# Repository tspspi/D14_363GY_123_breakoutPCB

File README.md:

# Breakout board for D14-363GY/123 CRT

This is a simple breakout board that includes impedance
matching networks (in this case tunes for 202 MHz - note
that this lies outside the specs for this tube) for deflection
plates and routes the high voltage and filament currents
to a DB9 connector. This PCB will be used as a mounting
structure for the CRT in a specific application (that
has nothing to do with running an oscilloscope or
visualizing signals)

The (inofficial) symbol and footprint used for the
D14-363GY/123 CRT pin layout is available in an
extra [KiCAD library](https://github.com/tspspi/tspikicadlibs)

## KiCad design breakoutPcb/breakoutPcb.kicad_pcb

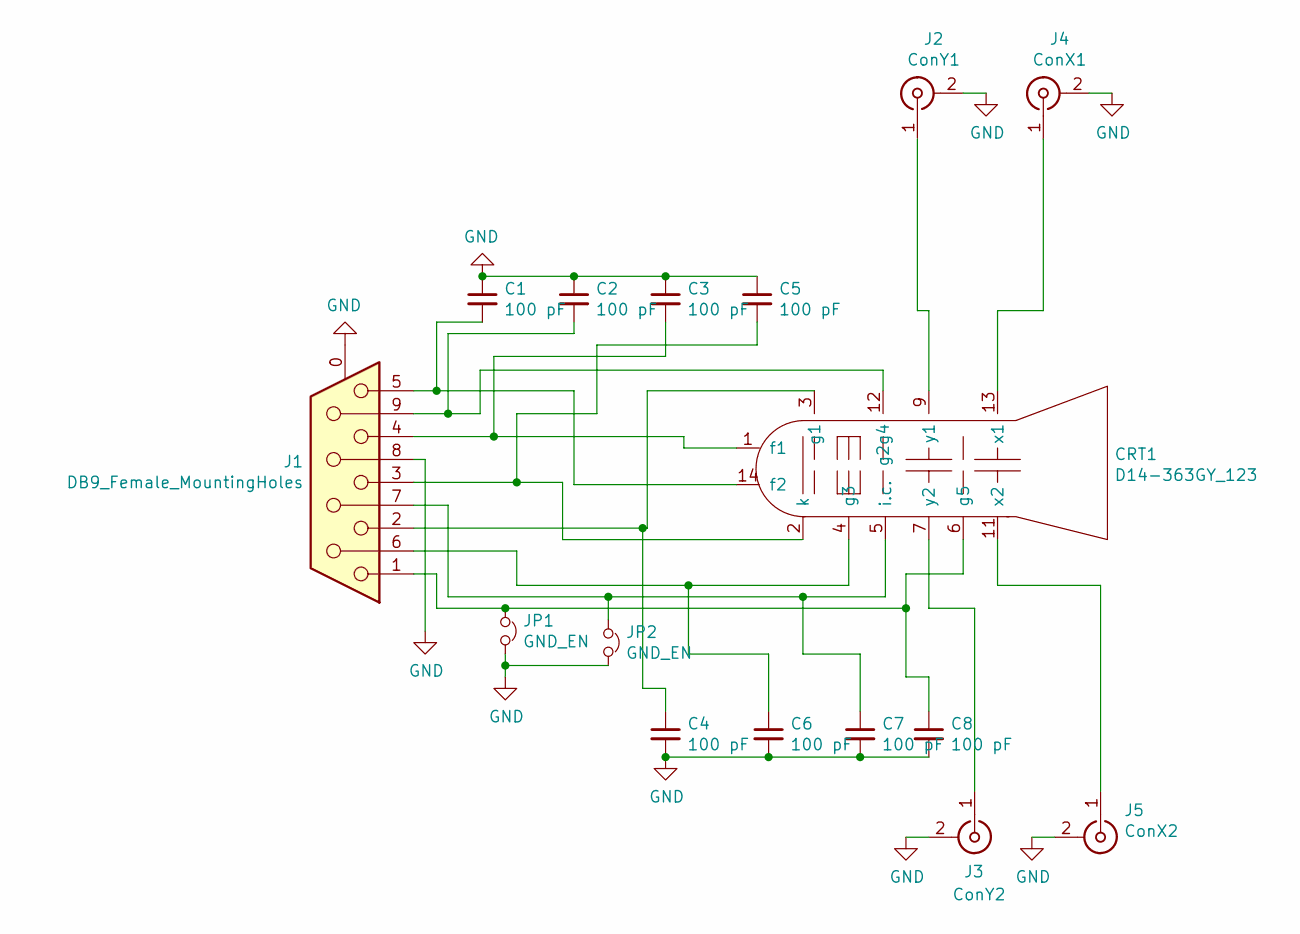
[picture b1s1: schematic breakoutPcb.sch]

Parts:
C1, C2, C3, C4, C5, C6, C7, C8: 100 pF; C_Disc_D5.0mm_W2.5mm_P5.00mm; FarnellNr C330C101JHG5TA
CRT1: D14-363GY_123; D14_363GY_123
J1: DB9_Female_MountingHoles; DSUB-9_Female_Vertical_P2.77x2.84mm_MountingHoles
J2: ConY1; SMA_Amphenol_132134-16_Vertical
J3: ConY2; SMA_Amphenol_132134-16_Vertical
J4: ConX1; SMA_Amphenol_132134-16_Vertical
J5: ConX2; SMA_Amphenol_132134-16_Vertical
JP1, JP2: GND_EN; R_0805_2012Metric

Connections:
GND: C1.1, C2.1, C3.1, C4.2, C5.1, C6.2, C7.2, C8.2, J1.0 (PAD), J1.8, J2.2 (Ext), J3.2 (Ext), J4.2 (Ext), J5.2 (Ext), JP1.2, JP2.2
unnamed: C1.2, CRT1.14 (f2), J1.5
unnamed: C2.2, CRT1.12 (g2g4), J1.9
unnamed: C3.2, CRT1.1 (f1), J1.4
unnamed: C4.1, CRT1.3 (g1), J1.2
unnamed: C5.2, CRT1.2 (k), J1.3
unnamed: C6.1, CRT1.4 (g3), J1.6
unnamed: C7.1, CRT1.5 (i.c.), J1.7, JP2.1
unnamed: C8.1, CRT1.6 (g5), J1.1, JP1.1
unnamed: CRT1.7 (y2), J3.1 (In)
unnamed: CRT1.9 (y1), J2.1 (In)
unnamed: CRT1.11 (x2), J5.1 (In)
unnamed: CRT1.13 (x1), J4.1 (In)

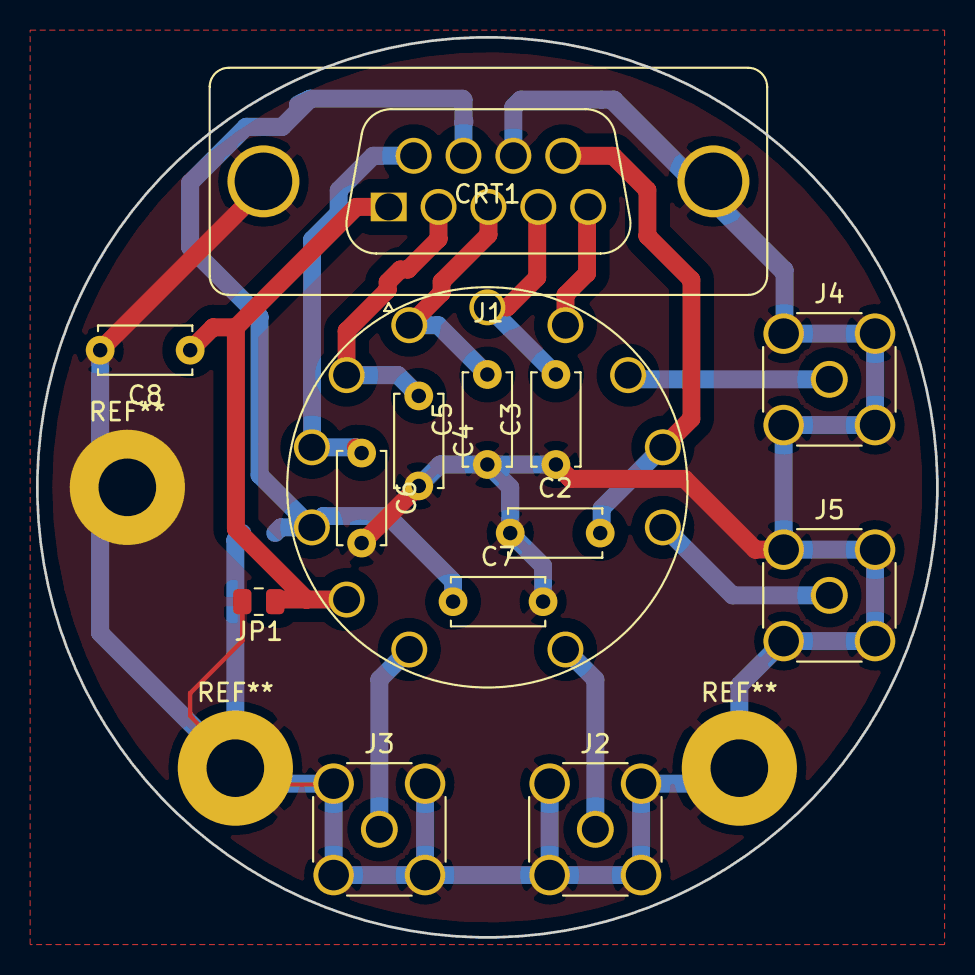
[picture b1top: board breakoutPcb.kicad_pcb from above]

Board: 2 copper layers, 50.0 x 50.0 mm, 15 parts (1 on the bottom side), 13 nets.

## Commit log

2022-04-06 Adding PCB layout image
2022-04-06 Rendering added to README
2022-04-06 Matching adapted to reality
2022-04-06 Back copper is now also GND ...
2022-04-06 Vanished mounting holes
2022-04-07 Symmetrized layout, changed connector assignment
2022-04-07 Generate Gerber files
2022-04-07 Minor change
2022-04-07 More even distances matching backplane
2022-04-07 Update gerber
2022-04-07 Larger holes for tube mount due to different connector
2022-04-19 Updated layout (no matching, with new decoupling)
2022-04-19 Updated Gerber
2022-04-19 Updated STEP
2022-04-29 Updated to latest version
2022-05-03 Bugfixes
2022-05-05 Updated gerber output
2022-05-05 Updated gerber files
2022-05-05 Prototel extensions, X1 format
